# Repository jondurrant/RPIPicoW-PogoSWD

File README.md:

# RPIPicoW-PogoSWD
Board to flash a Raspberry Pi Pico W via Pogo Pin connecting to SWD

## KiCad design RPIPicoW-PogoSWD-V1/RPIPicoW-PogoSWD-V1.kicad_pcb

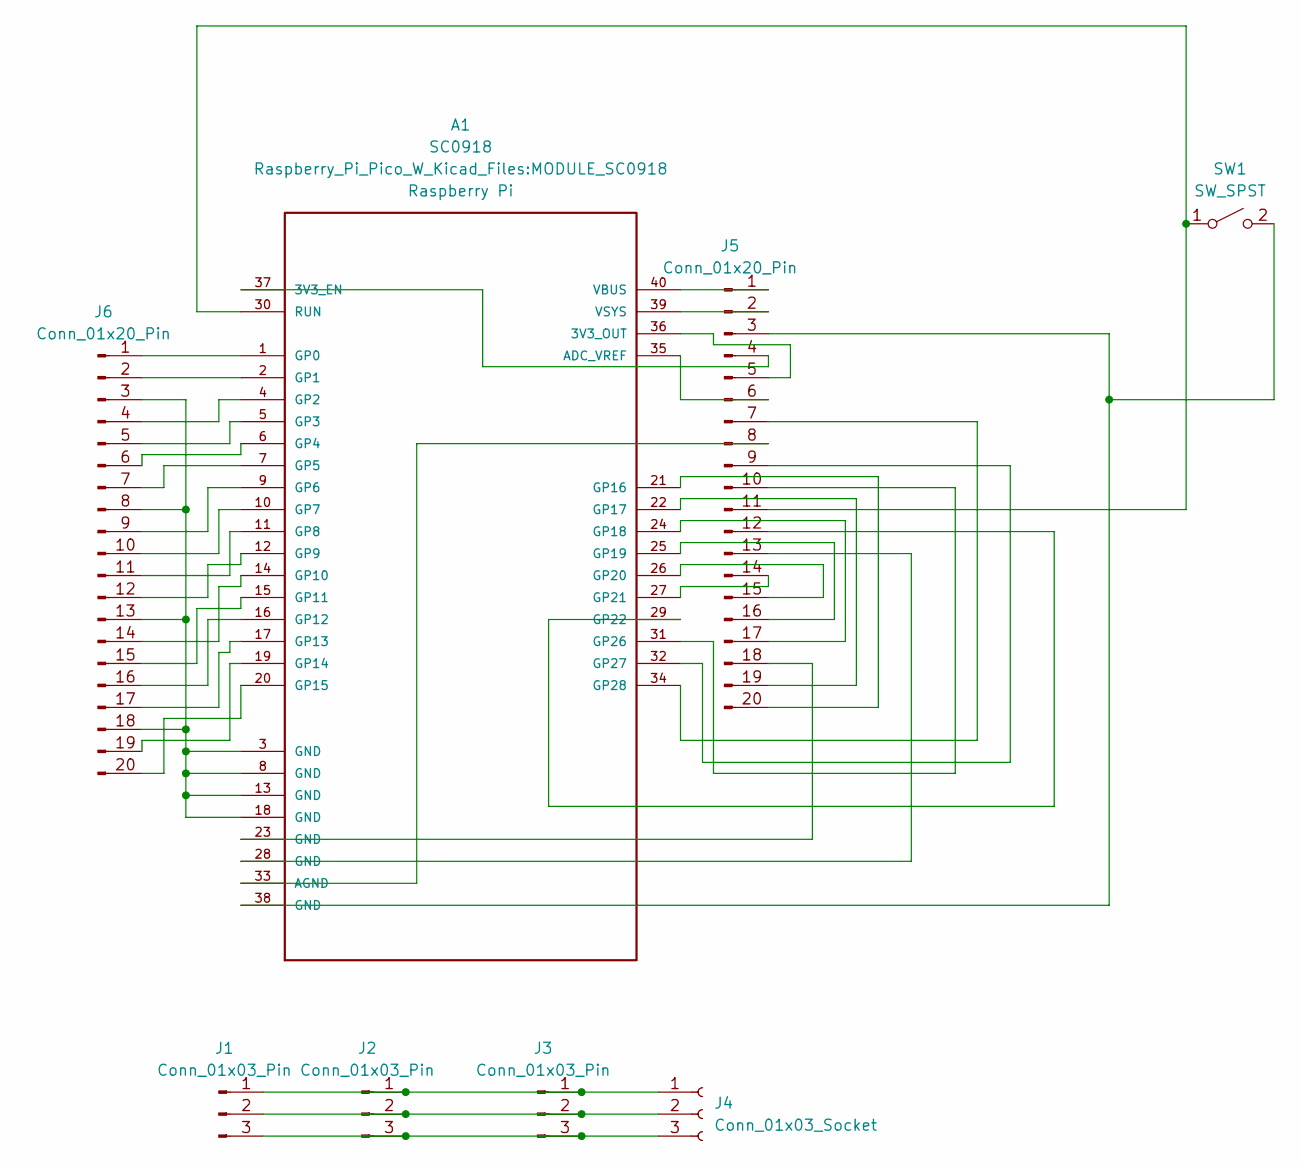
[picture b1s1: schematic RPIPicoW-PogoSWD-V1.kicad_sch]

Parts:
A1: SC0918; MODULE_SC0918; PARTREV 1.6
J1, J2, J3: Conn_01x03_Pin; PinHeader_1x03_P2.54mm_Vertical
J4: Conn_01x03_Socket; JST_SH_BM03B-SRSS-TB_1x03-1MP_P1.00mm_Vertical
J5, J6: Conn_01x20_Pin; PinHeader_1x20_P2.54mm_Vertical
SW1: SW_SPST; SW_PUSH_6mm

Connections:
unnamed: A1.37 (3V3_EN), J5.4
unnamed: A1.36 (3V3_OUT), J5.5
unnamed: A1.35 (ADC_VREF), J5.6
unnamed: A1.33 (AGND), J5.8
unnamed: A1.1 (GP0), J6.1
unnamed: A1.2 (GP1), J6.2
unnamed: A1.4 (GP2), J6.4
unnamed: A1.5 (GP3), J6.5
unnamed: A1.6 (GP4), J6.6
unnamed: A1.7 (GP5), J6.7
unnamed: A1.9 (GP6), J6.9
unnamed: A1.10 (GP7), J6.10
unnamed: A1.11 (GP8), J6.11
unnamed: A1.12 (GP9), J6.12
unnamed: A1.14 (GP10), J6.14
unnamed: A1.15 (GP11), J6.15
unnamed: A1.16 (GP12), J6.16
unnamed: A1.17 (GP13), J6.17
unnamed: A1.19 (GP14), J6.19
unnamed: A1.20 (GP15), J6.20
unnamed: A1.21 (GP16), J5.20
unnamed: A1.22 (GP17), J5.19
unnamed: A1.24 (GP18), J5.17
unnamed: A1.25 (GP19), J5.16
unnamed: A1.26 (GP20), J5.15
unnamed: A1.27 (GP21), J5.14
unnamed: A1.29 (GP22), J5.12
unnamed: A1.31 (GP26), J5.10
unnamed: A1.32 (GP27), J5.9
unnamed: A1.34 (GP28), J5.7
unnamed: A1.30 (RUN), J5.11, SW1.1 (A)
unnamed: A1.40 (VBUS), J5.1
unnamed: A1.39 (VSYS), J5.2
unnamed: J1.1, J2.1, J3.1, J4.1
unnamed: J1.2, J2.2, J3.2, J4.2
unnamed: J1.3, J2.3, J3.3, J4.3
unnamed: A1.38 (GND), J5.3, SW1.2 (B)
unnamed: A1.28 (GND), J5.13
unnamed: A1.23 (GND), J5.18
unnamed: A1.3 (GND), A1.8 (GND), A1.13 (GND), A1.18 (GND), J6.3, J6.8, J6.13, J6.18

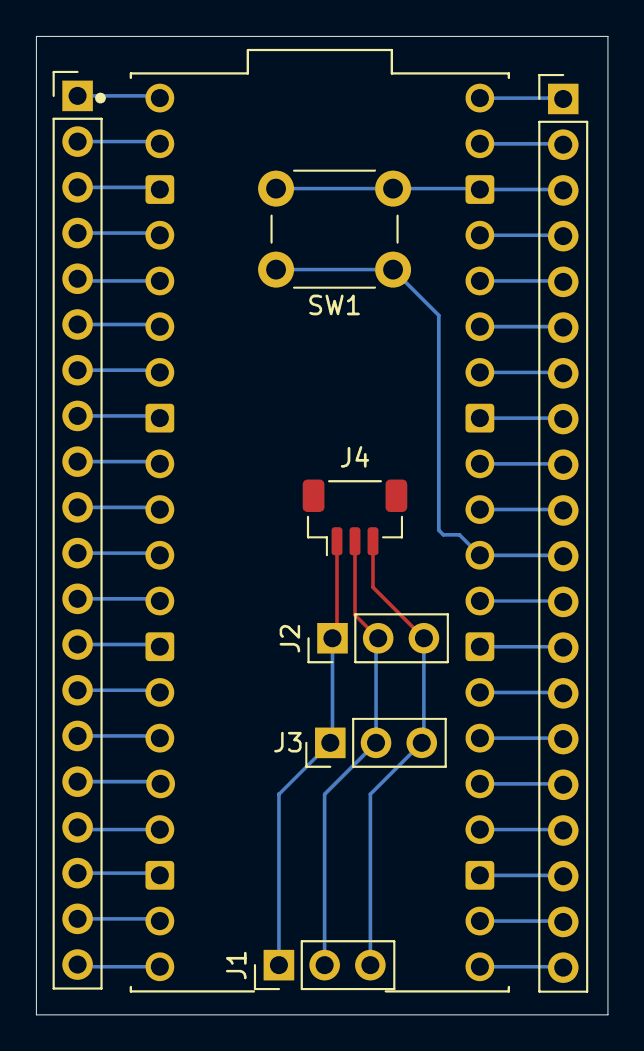
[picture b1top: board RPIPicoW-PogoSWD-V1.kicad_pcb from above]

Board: 2 copper layers, 31.8 x 54.4 mm, 8 parts (0 on the bottom side), 40 nets.

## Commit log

2025-04-17 Done
